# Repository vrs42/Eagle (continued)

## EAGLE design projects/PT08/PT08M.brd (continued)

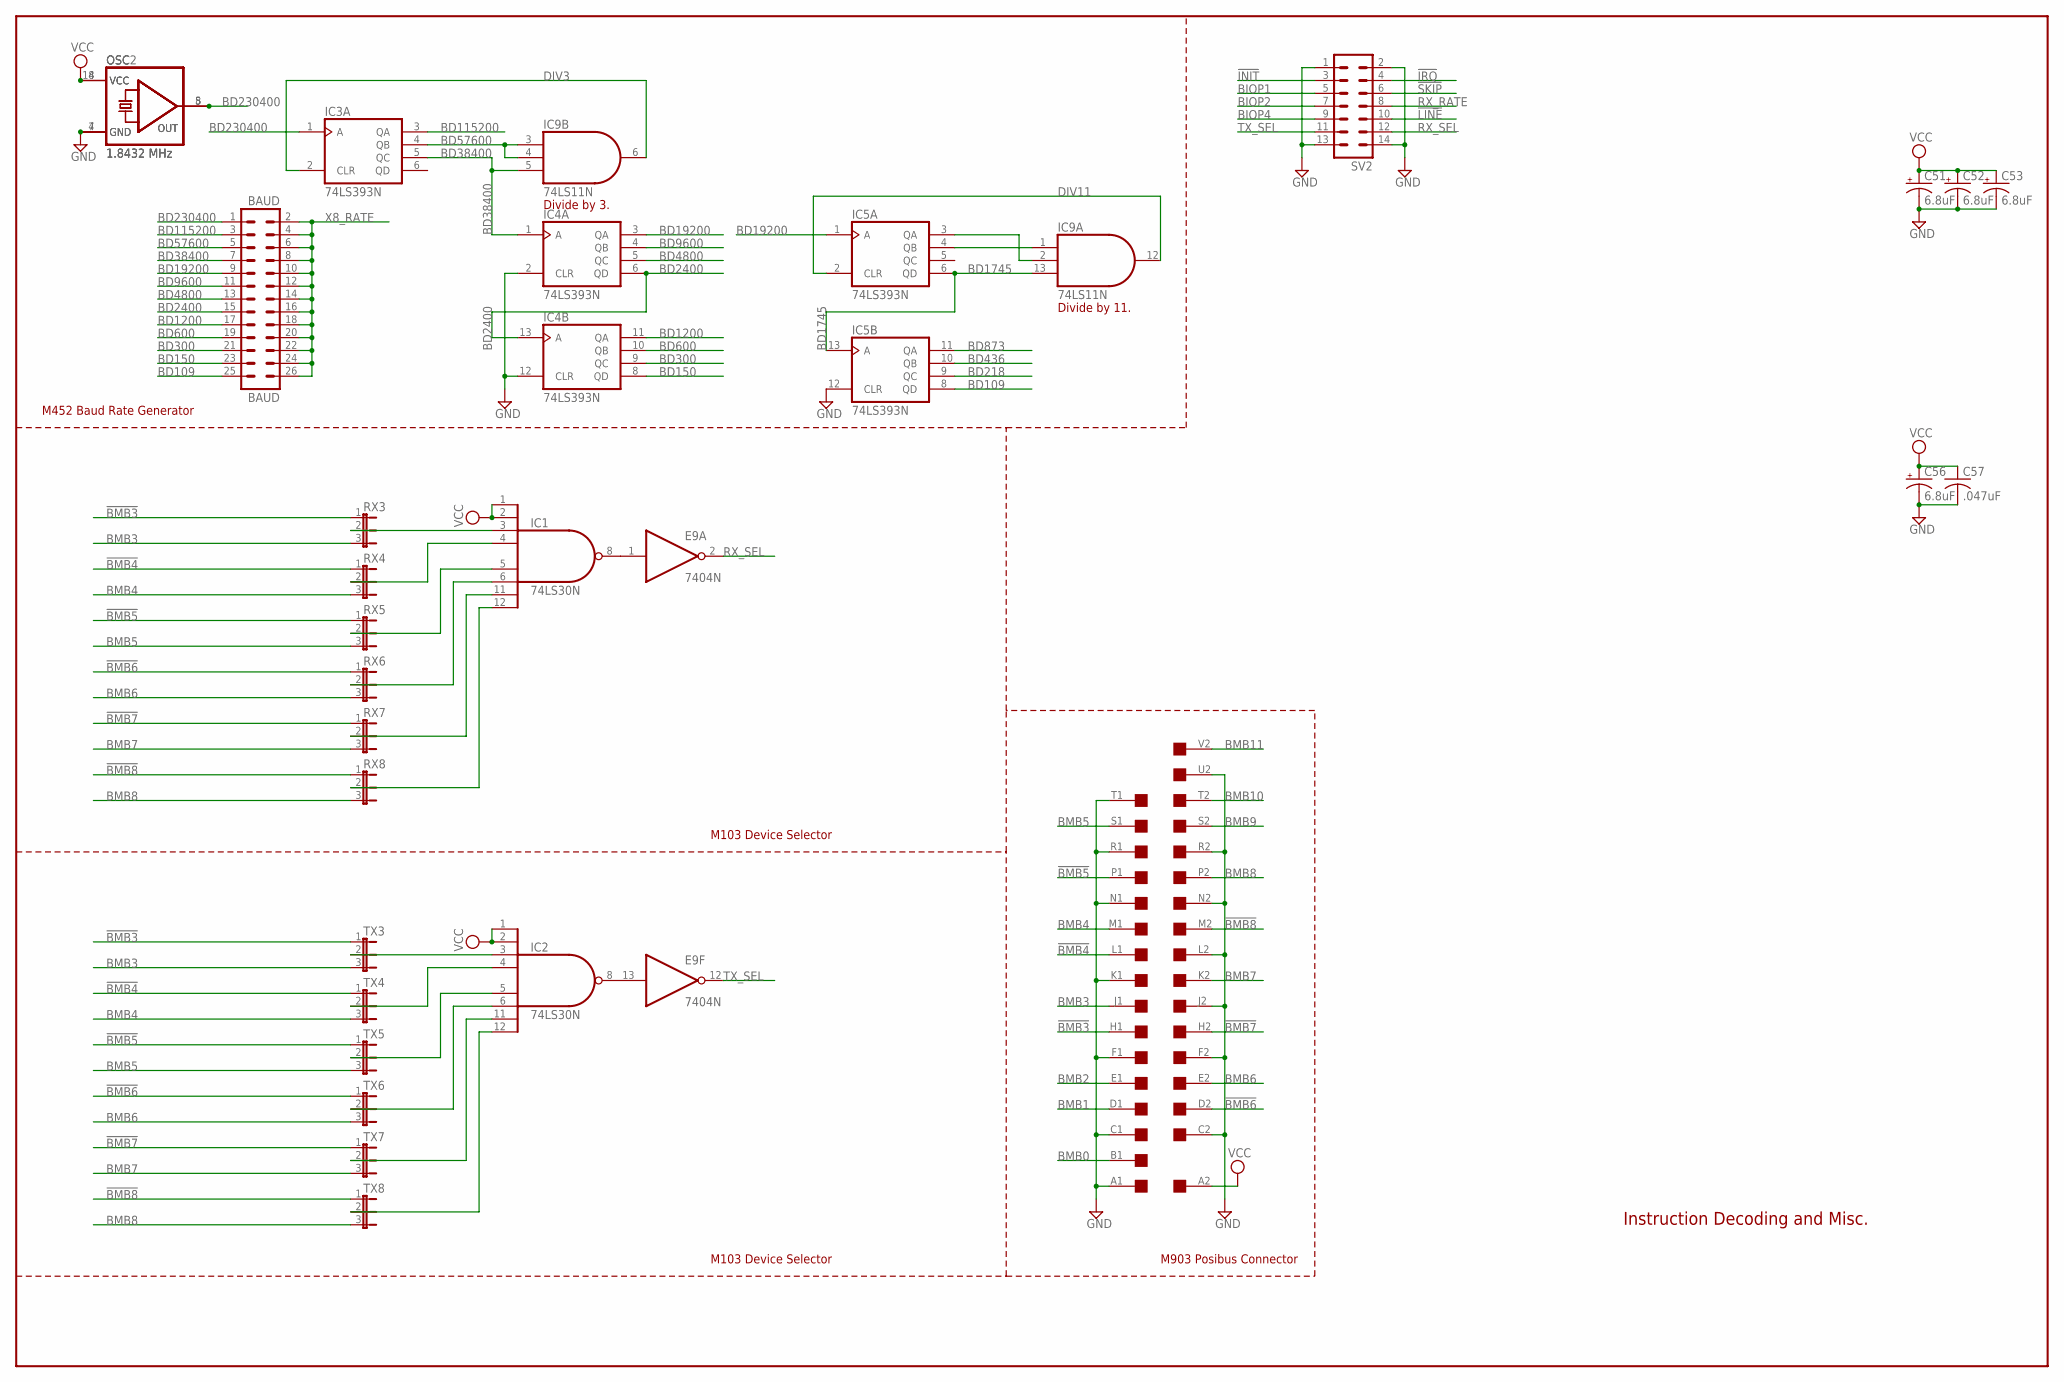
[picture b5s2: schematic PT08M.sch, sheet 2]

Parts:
BAUD: BAUD; MA13-2
C51, C52, C53, C56: 6.8uF; E12-8
C57: .047uF; C050-025X075
E9: 7404N; DIL14
IC1, IC2: 74LS30N; DIL14
IC3, IC4, IC5: 74LS393N; DIL14
IC9: 74LS11N; DIL14
N15: EDGE-2CONNECTOR; EDGE-CON2
OSC: 1.8432 MHz; DIL08S
OSC2: 1.8432 MHz; DIL14S
RX3, RX4, RX5, RX6, RX7, RX8: JP2
SV2: ML14L
TX3, TX4, TX5, TX6, TX7, TX8: JP2

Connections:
!BMB3: N15.H1, RX3.1, TX3.1
!BMB4: N15.L1, RX4.1, TX4.1
!BMB5: N15.P1, RX5.1, TX5.1
!BMB6: N15.D2, RX6.1, TX6.1
!BMB7: N15.H2, RX7.1, TX7.1
!BMB8: N15.M2, RX8.1, TX8.1
!INIT: SV2.3; also elsewhere on the board
!IRQ: SV2.4; also elsewhere on the board
!LINE: SV2.10; also elsewhere on the board
!RX_SEL: E9.1 (I), IC1.8 (O)
!SKIP: SV2.6; also elsewhere on the board
!TX_SEL: E9.13 (I), IC2.8 (O)
BD109: BAUD.25, IC5.8 (QD)
BD150: BAUD.23, IC4.8 (QD)
BD218: IC5.9 (QC)
BD300: BAUD.21, IC4.9 (QC)
BD436: IC5.10 (QB)
BD600: BAUD.19, IC4.10 (QB)
BD873: IC5.11 (QA)
BD1200: BAUD.17, IC4.11 (QA)
BD1745: IC5.6 (QD), IC5.13 (A), IC9.13 (I2)
BD2400: BAUD.15, IC4.6 (QD), IC4.13 (A)
BD4800: BAUD.13, IC4.5 (QC)
BD9600: BAUD.11, IC4.4 (QB)
BD19200: BAUD.9, IC4.3 (QA), IC5.1 (A)
BD38400: BAUD.7, IC3.5 (QC), IC4.1 (A), IC9.5 (I2)
BD57600: BAUD.5, IC3.4 (QB), IC9.3 (I0), IC9.4 (I1)
BD115200: BAUD.3, IC3.3 (QA)
BD230400: BAUD.1, IC3.1 (A), OSC.5 (OUT), OSC2.8 (OUT)
BIOP1: SV2.5; also elsewhere on the board
BIOP2: SV2.7; also elsewhere on the board
BIOP4: SV2.9; also elsewhere on the board
BMB0: N15.B1
BMB1: N15.D1
BMB2: N15.E1
BMB3: N15.J1, RX3.3, TX3.3
BMB4: N15.M1, RX4.3, TX4.3
BMB5: N15.S1, RX5.3, TX5.3
BMB6: N15.E2, RX6.3, TX6.3
BMB7: N15.K2, RX7.3, TX7.3
BMB8: N15.P2, RX8.3, TX8.3
BMB9: N15.S2
BMB10: N15.T2
BMB11: N15.V2
DIV3: IC3.2 (CLR), IC9.6 (O)
DIV11: IC5.2 (CLR), IC9.12 (O)
GND: C51.-, C52.-, C53.-, C56.-, C57.2, E9.7 (GND), IC1.7 (GND), IC2.7 (GND), IC3.7 (GND), IC4.2 (CLR), IC4.7 (GND), IC4.12 (CLR), IC5.7 (GND), IC5.12 (CLR), IC9.7 (GND), N15.A1, N15.C1, N15.C2, N15.F1, N15.F2, N15.J2, N15.K1, N15.L2, N15.N1, N15.N2, N15.R1, N15.R2, N15.T1, N15.U2, OSC.4 (GND), OSC2.7 (GND), SV2.1, SV2.2, SV2.13, SV2.14; also elsewhere on the board
unnamed: IC2.4 (I3), TX4.2
unnamed: IC1.3 (I2), RX3.2
unnamed: IC1.4 (I3), RX4.2
unnamed: IC2.6 (I5), TX6.2
unnamed: IC1.5 (I4), RX5.2
unnamed: IC2.5 (I4), TX5.2
unnamed: IC2.12 (I7), TX8.2
unnamed: IC2.11 (I6), TX7.2
unnamed: IC5.3 (QA), IC9.2 (I1)
unnamed: IC2.3 (I2), TX3.2
unnamed: IC1.12 (I7), RX8.2
unnamed: IC5.4 (QB), IC9.1 (I0)
unnamed: IC1.11 (I6), RX7.2
unnamed: IC1.6 (I5), RX6.2
RX_RATE: SV2.8; also elsewhere on the board
RX_SEL: E9.2 (O), SV2.12; also elsewhere on the board
TX_SEL: E9.12 (O), SV2.11; also elsewhere on the board
VCC: C51.+, C52.+, C53.+, C56.+, C57.1, E9.14 (VCC), IC1.1 (I0), IC1.2 (I1), IC1.14 (VCC), IC2.1 (I0), IC2.2 (I1), IC2.14 (VCC), IC3.14 (VCC), IC4.14 (VCC), IC5.14 (VCC), IC9.14 (VCC), N15.A2, OSC.8 (VCC), OSC2.14 (VCC); also elsewhere on the board
X8_RATE: BAUD.2, BAUD.4, BAUD.6, BAUD.8, BAUD.10, BAUD.12, BAUD.14, BAUD.16, BAUD.18, BAUD.20, BAUD.22, BAUD.24, BAUD.26

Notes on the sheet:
Instruction Decoding and Misc.
M452 Baud Rate Generator
M103 Device Selector
M903 Posibus Connector
Divide by 11.
Divide by 3.

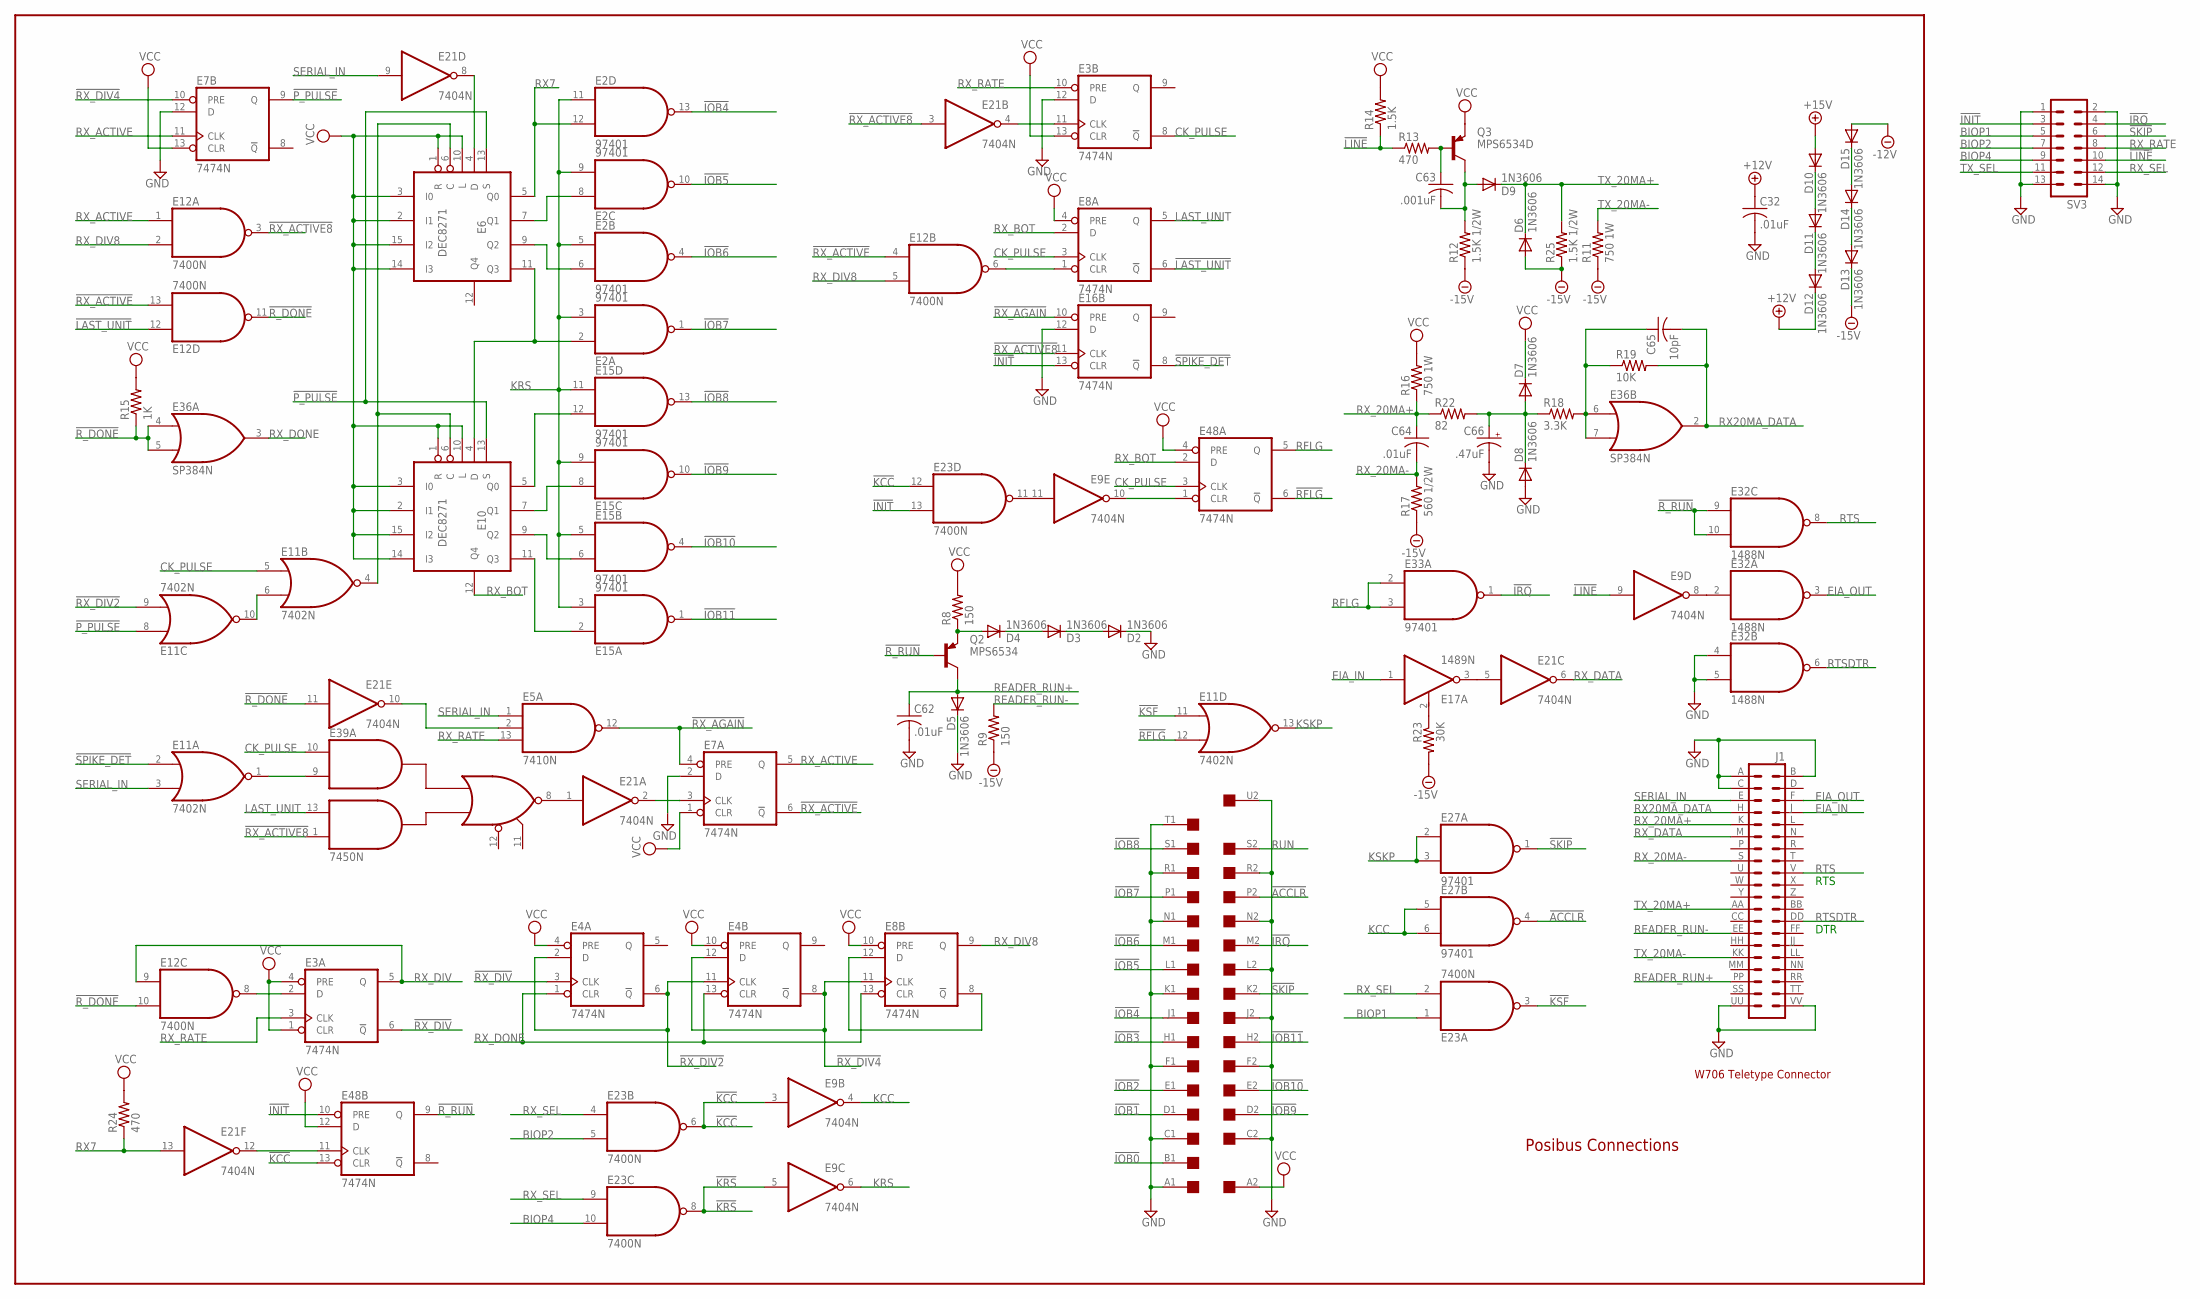
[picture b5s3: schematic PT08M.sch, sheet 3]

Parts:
C32, C62, C64: .01uF; C050-025X075
C63: .001uF; C050-025X075
C65: 10pF; C050-025X075
C66: .47uF; E15-5
D2, D3, D4, D5, D6, D7, D8, D9, D10, D11, D12, D13, D14, D15: 1N3606; DO35-10
E2, E15, E27, E33: 97401; DIL14
E3, E4, E7, E8, E16, E48: 7474N; DIL14
E5: 7410N; DIL14
E6, E10: DEC8271; DIL16
E9, E21: 7404N; DIL14
E11: 7402N; DIL14
E12, E23: 7400N; DIL14
E17: 1489N; DIL14
E32: 1488N; DIL14
E36: SP384N; DIL14
E39: 7450N; DIL14
J1: DEC40PINH
N16: EDGE-2CONNECTOR; EDGE-CON2
Q2: MPS6534; TO5
Q3: MPS6534D; TO5
R8, R9: 150; 0207/10
R11, R16: 750 1W; 0617/17
R12, R25: 1.5K 1/2W; 0411/15
R13, R24: 470; 0207/10
R14: 1.5K; 0207/10
R15: 1K; 0207/10
R17: 560 1/2W; 0411/15
R18: 3.3K; 0207/10
R19: 10K; 0207/10
R22: 82; 0207/10
R23: 30K; 0207/10
SV3: ML14L

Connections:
!ACCLR: E27.4 (O), N16.P2
!INIT: E16.13 (CLR), E23.13 (I1), E48.10 (PRE), SV3.3; also elsewhere on the board
!IOB0: N16.B1
!IOB1: N16.D1
!IOB2: N16.E1
!IOB3: N16.H1
!IOB4: E2.13 (O), N16.J1
!IOB5: E2.10 (O), N16.L1
!IOB6: E2.4 (O), N16.M1
!IOB7: E2.1 (O), N16.P1
!IOB8: E15.13 (O), N16.S1
!IOB9: E15.10 (O), N16.D2
!IOB10: E15.4 (O), N16.E2
!IOB11: E15.1 (O), N16.H2
!IRQ: E33.1 (O), N16.M2, SV3.4; also elsewhere on the board
!KCC: E9.3 (I), E23.6 (O), E23.12 (I0), E48.13 (CLR)
!KRS: E9.5 (I), E23.8 (O)
!KSF: E11.11 (I0), E23.3 (O)
!LAST_UNIT: E8.6 (!Q), E12.12 (I0)
!LINE: E9.9 (I), R13.1, R14.1, SV3.10; also elsewhere on the board
!P_PULSE: E6.13 (S), E7.9 (Q), E10.13 (S), E11.8 (I0)
!RFLG: E11.12 (I1), E48.6 (!Q)
!RX_ACTIVE: E7.6 (!Q), E12.4 (I0), E12.13 (I1)
!RX_ACTIVE8: E12.3 (O), E16.11 (CLK), E21.3 (I), E39.1 (I4)
!RX_AGAIN: E5.12 (O), E7.4 (PRE), E16.10 (PRE)
!RX_DIV: E3.6 (!Q), E4.3 (CLK)
!RX_DIV2: E4.2 (D), E4.6 (!Q), E4.11 (CLK), E11.9 (I1)
!RX_DIV4: E4.8 (!Q), E4.12 (D), E7.10 (PRE), E8.11 (CLK)
!R_DONE: E12.10 (I1), E12.11 (O), E21.11 (I), E36.4 (I0), E36.5 (I1), R15.1
!R_RUN: E32.9 (I0), E32.10 (I1), E48.9 (Q), Q2.2 (B)
!SKIP: E27.1 (O), N16.K2, SV3.6; also elsewhere on the board
!SPIKE_DET: E11.2 (I0), E16.8 (!Q)
+12V: C32.1, D12.C, E32.14 (+12V)
+15V: D10.A
-12V: D15.A, E32.1 (-12V)
-15V: D6.A, D13.C, R9.1, R11.1, R12.1, R17.1, R23.2, R25.1
BIOP1: E23.1 (I0), SV3.5; also elsewhere on the board
BIOP2: E23.5 (I1), SV3.7; also elsewhere on the board
BIOP4: E23.10 (I1), SV3.9; also elsewhere on the board
CK_PULSE: E3.8 (!Q), E8.3 (CLK), E11.5 (I0), E39.10 (I1), E48.3 (CLK)
EIA_IN: E17.1 (I), J1.J (8)
EIA_OUT: E32.3 (O), J1.F (6)
GND: C32.2, C62.2, C66.-, D2.C, D5.C, D8.A, E2.7 (GND), E3.7 (GND), E3.12 (D), E4.7 (GND), E5.7 (GND), E6.8 (GND), E7.2 (D), E7.7 (GND), E7.12 (D), E8.7 (GND), E9.7 (GND), E10.8 (GND), E11.7 (GND), E12.7 (GND), E15.7 (GND), E16.7 (GND), E16.12 (D), E17.7 (GND), E21.7 (GND), E23.7 (GND), E27.7 (GND), E32.4 (I0), E32.5 (I1), E32.7 (GND), E33.7 (GND), E36.1 (GND), E39.7 (GND), E48.7 (GND), J1.A (1), J1.B (2), J1.C (3), J1.UU (39), J1.VV (40), N16.A1, N16.C1, N16.C2, N16.F1, N16.F2, N16.J2, N16.K1, N16.L2, N16.N1, N16.N2, N16.R1, N16.R2, N16.T1, N16.U2, SV3.1, SV3.2, SV3.13, SV3.14; also elsewhere on the board
KCC: E9.4 (O), E27.5 (I0), E27.6 (I1)
KRS: E2.3 (I1), E2.5 (I0), E2.9 (I1), E2.11 (I0), E9.6 (O), E15.3 (I1), E15.5 (I0), E15.9 (I1), E15.11 (I0)
KSKP: E11.13 (O), E27.2 (I0), E27.3 (I1)
LAST_UNIT: E8.5 (Q), E39.13 (I3)
unnamed: E9.8 (O), E32.2 (I)
unnamed: E21.12 (O), E48.11 (CLK)
unnamed: E9.10 (O), E48.1 (CLR)
unnamed: E9.11 (I), E23.11 (O)
unnamed: D2.A, D3.C
unnamed: E2.8 (I0), E6.7 (Q1)
unnamed: E2.2 (I0), E6.11 (Q3), E10.4 (D)
unnamed: E2.6 (I1), E6.9 (Q2)
unnamed: E10.5 (Q0), E15.12 (I1)
unnamed: E10.7 (Q1), E15.8 (I0)
unnamed: E10.9 (Q2), E15.6 (I1)
unnamed: E10.11 (Q3), E15.2 (I0)
unnamed: E6.6 (C), E10.6 (C), E11.4 (O)
unnamed: E11.6 (I1), E11.10 (O)
unnamed: E6.4 (D), E21.8 (O)
unnamed: E7.3 (CLK), E21.2 (O)
unnamed: E21.1 (I), E39.8 (O)
unnamed: C63.2, D9.A, Q3.3 (C), R12.2
unnamed: E3.2 (D), E12.8 (O)
unnamed: E17.2 (RC), R23.1
unnamed: E5.2 (I1), E21.10 (O)
unnamed: D13.A, D14.C
unnamed: E11.1 (O), E39.9 (I2)
unnamed: E3.11 (CLK), E21.4 (O)
unnamed: E17.3 (O), E21.5 (I)
unnamed: E8.8 (!Q), E8.12 (D)
unnamed: E8.1 (CLR), E12.6 (O)
unnamed: D4.A, Q2.1 (E), R8.1
unnamed: D3.A, D4.C
unnamed: D14.A, D15.C
unnamed: C66.+, D7.A, D8.C, R18.1, R22.2
unnamed: D10.C, D11.A
unnamed: D11.C, D12.A
unnamed: C65.1, E36.6 (I0), E36.7 (I1), R18.2, R19.1
unnamed: C63.1, Q3.2 (B), R13.2
READER_RUN+: C62.1, D5.A, J1.PP (35), Q2.3 (C)
READER_RUN-: J1.EE (27), R9.2
RFLG: E33.2 (I0), E33.3 (I1), E48.5 (Q)
RTS: E32.8 (O), J1.V (18)
RTSDTR: E32.6 (O), J1.DD (26)
RUN: N16.S2
RX7: E2.12 (I1), E6.5 (Q0), E21.13 (I), R24.1
RX20MA_DATA: C65.2, E36.2 (O), J1.H (7), R19.2
RX_20MA+: C64.1, J1.K (9), R16.1, R22.1
RX_20MA-: C64.2, J1.S (15), R17.2
RX_ACTIVE: E7.5 (Q), E7.11 (CLK), E12.1 (I0)
RX_BOT: E8.2 (D), E10.12 (Q4), E48.2 (D)
RX_DATA: E21.6 (O), J1.M (11)
RX_DIV: E3.5 (Q), E12.9 (I0)
RX_DIV8: E8.9 (Q), E12.2 (I1), E12.5 (I1)
RX_DONE: E4.1 (CLR), E4.13 (CLR), E8.13 (CLR), E36.3 (O)
RX_RATE: E3.3 (CLK), E3.10 (PRE), E5.13 (I2), SV3.8; also elsewhere on the board
RX_SEL: E23.2 (I1), E23.4 (I0), E23.9 (I0), SV3.12; also elsewhere on the board
SERIAL_IN: E5.1 (I0), E11.3 (I1), E21.9 (I), J1.E (5)
TX_20MA+: D6.C, D9.C, J1.AA (23), R25.2
TX_20MA-: J1.KK (31), R11.2
TX_SEL: SV3.11; also elsewhere on the board
VCC: D7.C, E2.14 (VCC), E3.1 (CLR), E3.4 (PRE), E3.13 (CLR), E3.14 (VCC), E4.4 (PRE), E4.10 (PRE), E4.14 (VCC), E5.14 (VCC), E6.1 (R), E6.2 (I1), E6.3 (I0), E6.10 (L), E6.14 (I3), E6.15 (I2), E6.16 (VCC), E7.1 (CLR), E7.13 (CLR), E7.14 (VCC), E8.4 (PRE), E8.10 (PRE), E8.14 (VCC), E9.14 (VCC), E10.1 (R), E10.2 (I1), E10.3 (I0), E10.10 (L), E10.14 (I3), E10.15 (I2), E10.16 (VCC), E11.14 (VCC), E12.14 (VCC), E15.14 (VCC), E16.14 (VCC), E17.14 (VCC), E21.14 (VCC), E23.14 (VCC), E27.14 (VCC), E33.14 (VCC), E36.8 (VCC), E39.14 (VCC), E48.4 (PRE), E48.12 (D), E48.14 (VCC), N16.A2, Q3.1 (E), R8.2, R14.2, R15.2, R16.2, R24.2; also elsewhere on the board

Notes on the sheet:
Posibus Connections
RTS
DTR
W706 Teletype Connector

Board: 4 copper layers, 143 parts (0 on the bottom side), 190 nets, no tracks yet.

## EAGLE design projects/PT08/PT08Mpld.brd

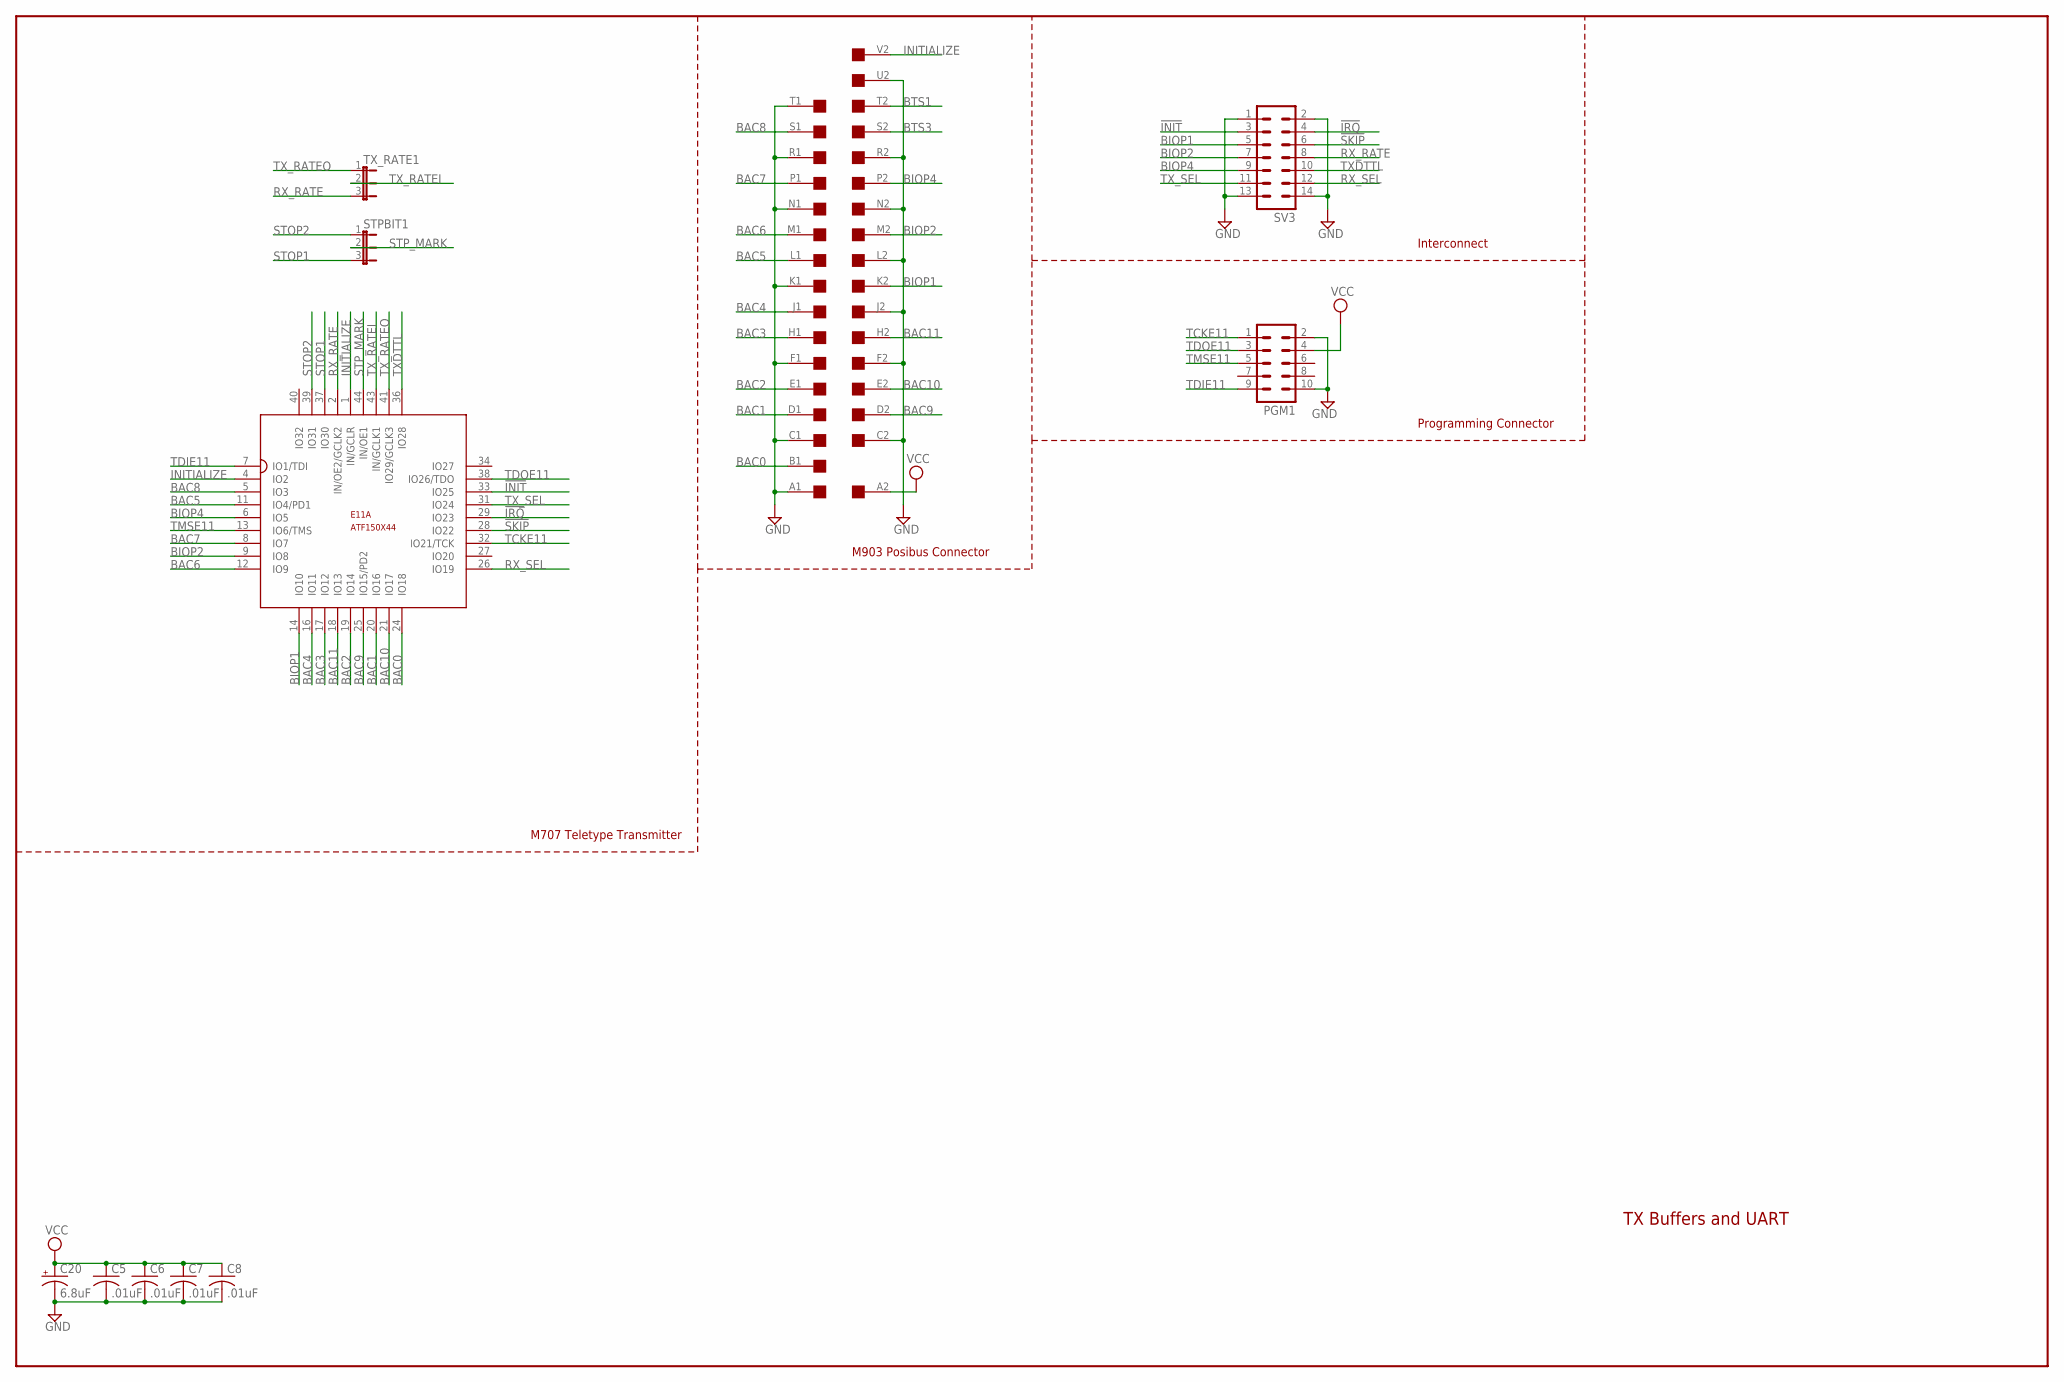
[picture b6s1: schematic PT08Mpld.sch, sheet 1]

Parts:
BAC: EDGE-2CONNECTOR; EDGE-CON2
C5, C6, C7, C8: .01uF; C050-025X075
C20: 6.8uF; E12-8
E11: ATF150X44; 3M44
PGM1: ML10
STPBIT1: JP2
SV3: ML14L
TX_RATE1: JP2

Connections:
!INIT: E11.33 (IO25), SV3.3; also elsewhere on the board
!IRQ: E11.29 (IO23), SV3.4; also elsewhere on the board
!SKIP: E11.28 (IO22), SV3.6; also elsewhere on the board
BAC0: BAC.B1, E11.24 (IO18)
BAC1: BAC.D1, E11.20 (IO16)
BAC2: BAC.E1, E11.19 (IO14)
BAC3: BAC.H1, E11.17 (IO12)
BAC4: BAC.J1, E11.16 (IO11)
BAC5: BAC.L1, E11.11 (IO4/PD1)
BAC6: BAC.M1, E11.12 (IO9)
BAC7: BAC.P1, E11.8 (IO7)
BAC8: BAC.S1, E11.5 (IO3)
BAC9: BAC.D2, E11.25 (IO15/PD2)
BAC10: BAC.E2, E11.21 (IO17)
BAC11: BAC.H2, E11.18 (IO13)
BIOP1: BAC.K2, E11.14 (IO10), SV3.5; also elsewhere on the board
BIOP2: BAC.M2, E11.9 (IO8), SV3.7; also elsewhere on the board
BIOP4: BAC.P2, E11.6 (IO5), SV3.9; also elsewhere on the board
BTS1: BAC.T2
BTS3: BAC.S2
GND: BAC.A1, BAC.C1, BAC.C2, BAC.F1, BAC.F2, BAC.J2, BAC.K1, BAC.L2, BAC.N1, BAC.N2, BAC.R1, BAC.R2, BAC.T1, BAC.U2, C5.2, C6.2, C7.2, C8.2, C20.-, E11.10 (GND), E11.22 (GND), E11.30 (GND), E11.42 (GND), PGM1.2, PGM1.10, SV3.1, SV3.2, SV3.13, SV3.14; also elsewhere on the board
INITIALIZE: BAC.V2, E11.1 (IN/GCLR), E11.4 (IO2)
RX_RATE: E11.2 (IN/OE2/GCLK2), SV3.8, TX_RATE1.3; also elsewhere on the board
RX_SEL: E11.26 (IO19), SV3.12; also elsewhere on the board
STOP1: E11.37 (IO30), STPBIT1.3
STOP2: E11.39 (IO31), STPBIT1.1
STP_MARK: E11.44 (IN/OE1), STPBIT1.2
TCKE11: E11.32 (IO21/TCK), PGM1.1
TDIE11: E11.7 (IO1/TDI), PGM1.9
TDOE11: E11.38 (IO26/TDO), PGM1.3
TMSE11: E11.13 (IO6/TMS), PGM1.5
TXDTTL: E11.36 (IO28), SV3.10; also elsewhere on the board
TX_RATEI: E11.43 (IN/GCLK1), TX_RATE1.2
TX_RATEO: E11.41 (IO29/GCLK3), TX_RATE1.1
TX_SEL: E11.31 (IO24), SV3.11; also elsewhere on the board
VCC: BAC.A2, C5.1, C6.1, C7.1, C8.1, C20.+, E11.3 (VCC), E11.15 (VCC), E11.23 (VCC), E11.35 (VCC), PGM1.4; also elsewhere on the board

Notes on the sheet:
TX Buffers and UART
M707 Teletype Transmitter
M903 Posibus Connector
Programming Connector
Interconnect

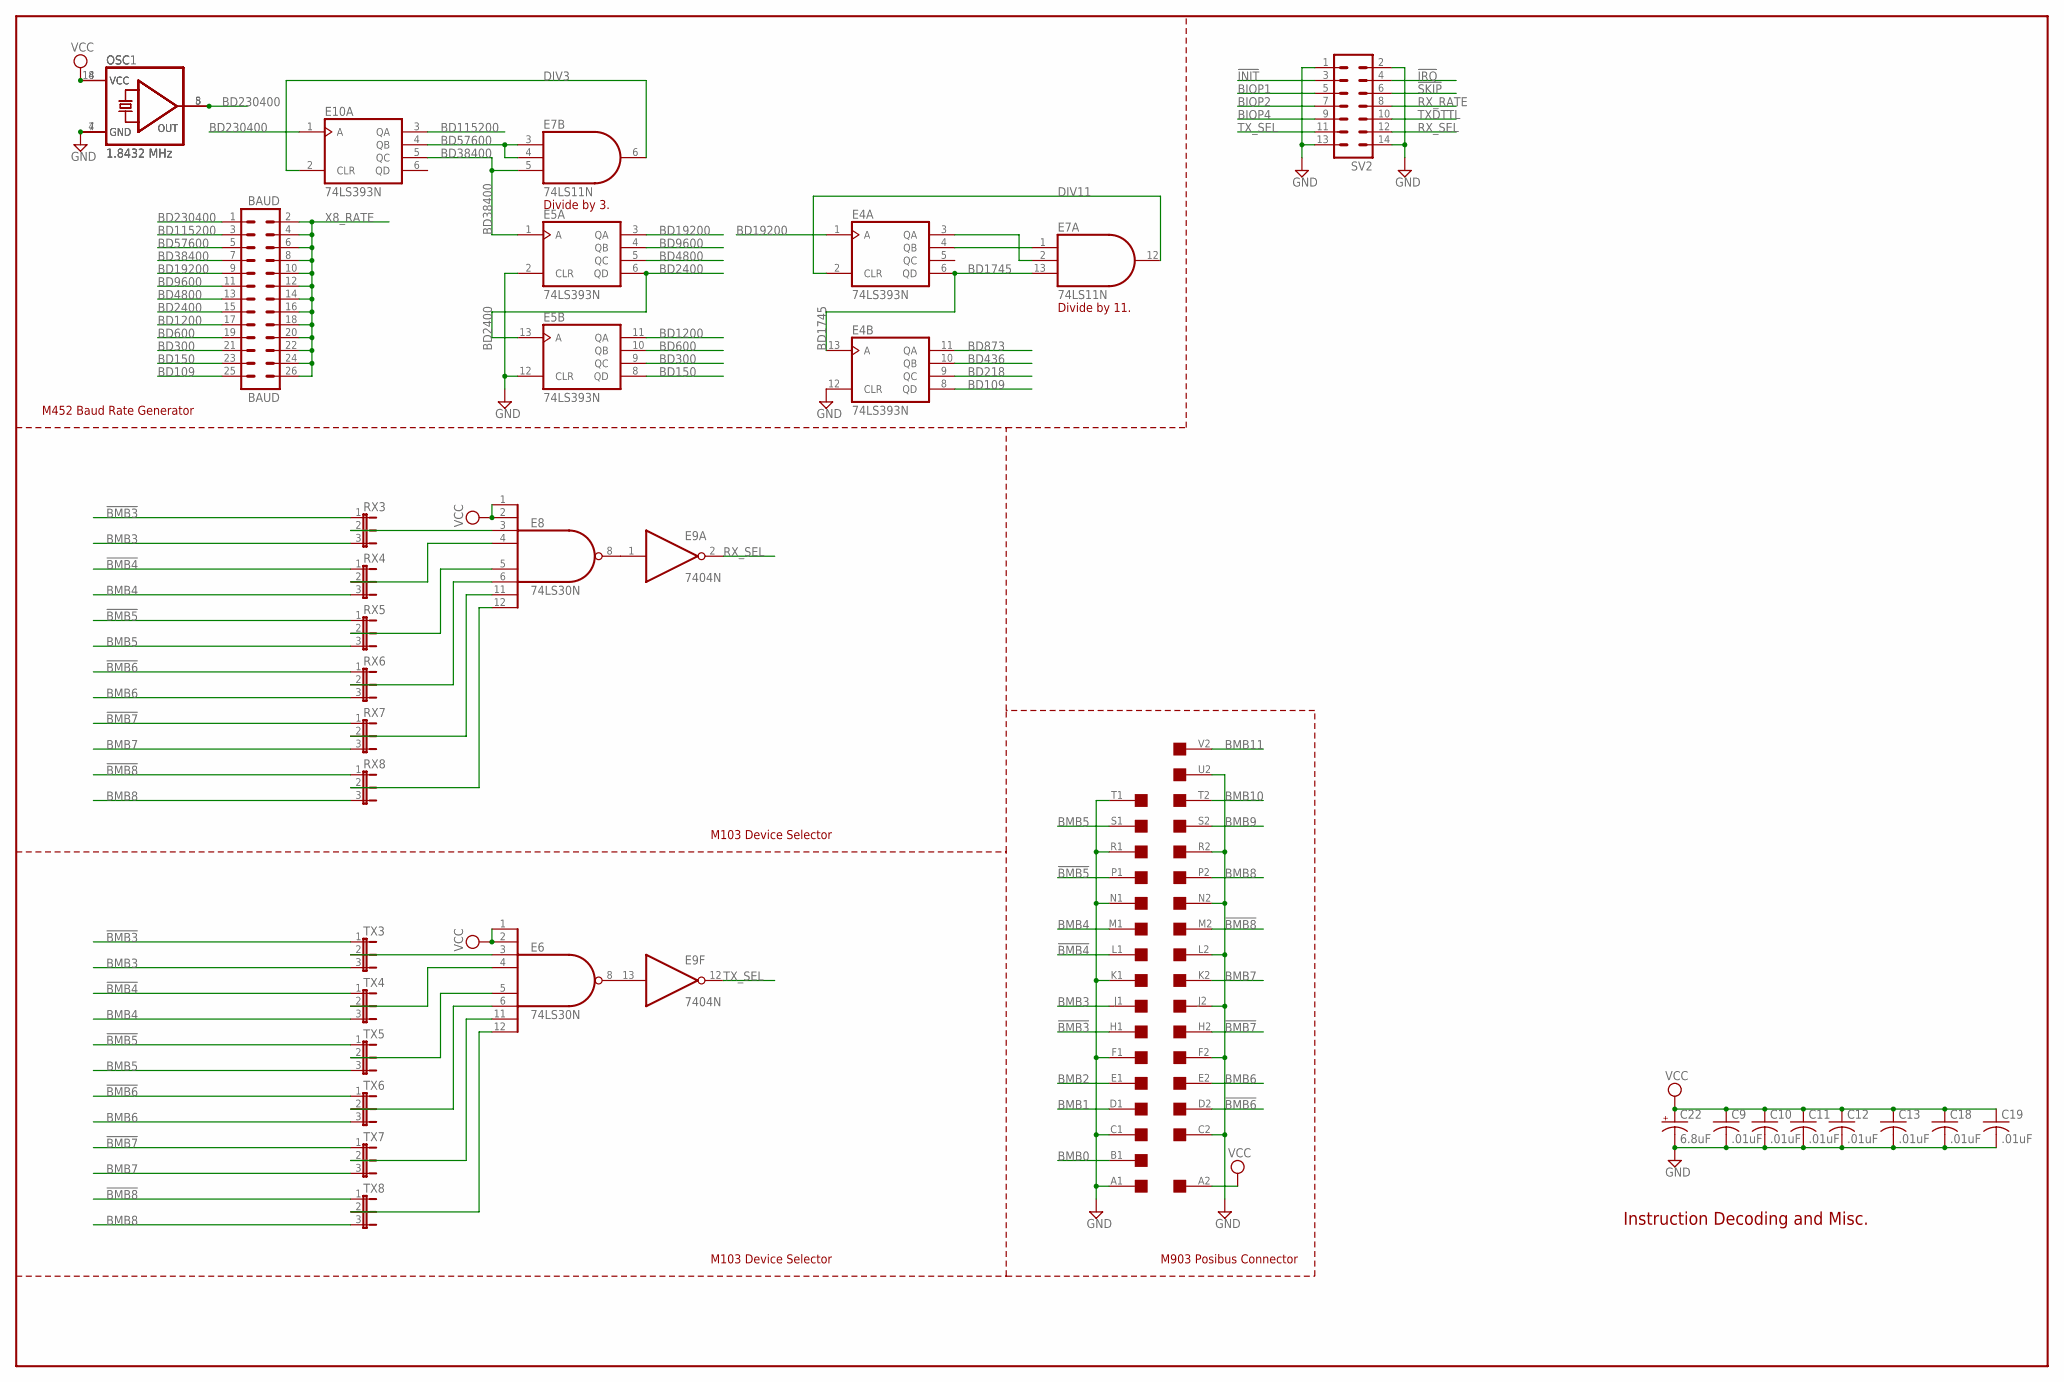
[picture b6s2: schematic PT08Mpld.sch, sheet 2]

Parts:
BAUD: BAUD; MA13-2
BMB: EDGE-2CONNECTOR; EDGE-CON2
C9, C10, C11, C12, C13, C18, C19: .01uF; C050-025X075
C22: 6.8uF; E12-8
E4, E5, E10: 74LS393N; DIL14
E6, E8: 74LS30N; DIL14
E7: 74LS11N; DIL14
E9: 7404N; DIL14
OSC: 1.8432 MHz; DIL08S
OSC1: 1.8432 MHz; DIL14S
RX3, RX4, RX5, RX6, RX7, RX8: JP2
SV2: ML14L
TX3, TX4, TX5, TX6, TX7, TX8: JP2

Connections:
!BMB3: BMB.H1, RX3.1, TX3.1
!BMB4: BMB.L1, RX4.1, TX4.1
!BMB5: BMB.P1, RX5.1, TX5.1
!BMB6: BMB.D2, RX6.1, TX6.1
!BMB7: BMB.H2, RX7.1, TX7.1
!BMB8: BMB.M2, RX8.1, TX8.1
!INIT: SV2.3; also elsewhere on the board
!IRQ: SV2.4; also elsewhere on the board
!RX_SEL: E8.8 (O), E9.1 (I)
!SKIP: SV2.6; also elsewhere on the board
!TX_SEL: E6.8 (O), E9.13 (I)
BD109: BAUD.25, E4.8 (QD)
BD150: BAUD.23, E5.8 (QD)
BD218: E4.9 (QC)
BD300: BAUD.21, E5.9 (QC)
BD436: E4.10 (QB)
BD600: BAUD.19, E5.10 (QB)
BD873: E4.11 (QA)
BD1200: BAUD.17, E5.11 (QA)
BD1745: E4.6 (QD), E4.13 (A), E7.13 (I2)
BD2400: BAUD.15, E5.6 (QD), E5.13 (A)
BD4800: BAUD.13, E5.5 (QC)
BD9600: BAUD.11, E5.4 (QB)
BD19200: BAUD.9, E4.1 (A), E5.3 (QA)
BD38400: BAUD.7, E5.1 (A), E7.5 (I2), E10.5 (QC)
BD57600: BAUD.5, E7.3 (I0), E7.4 (I1), E10.4 (QB)
BD115200: BAUD.3, E10.3 (QA)
BD230400: BAUD.1, E10.1 (A), OSC.5 (OUT), OSC1.8 (OUT)
BIOP1: SV2.5; also elsewhere on the board
BIOP2: SV2.7; also elsewhere on the board
BIOP4: SV2.9; also elsewhere on the board
BMB0: BMB.B1
BMB1: BMB.D1
BMB2: BMB.E1
BMB3: BMB.J1, RX3.3, TX3.3
BMB4: BMB.M1, RX4.3, TX4.3
BMB5: BMB.S1, RX5.3, TX5.3
BMB6: BMB.E2, RX6.3, TX6.3
BMB7: BMB.K2, RX7.3, TX7.3
BMB8: BMB.P2, RX8.3, TX8.3
BMB9: BMB.S2
BMB10: BMB.T2
BMB11: BMB.V2
DIV3: E7.6 (O), E10.2 (CLR)
DIV11: E4.2 (CLR), E7.12 (O)
GND: BMB.A1, BMB.C1, BMB.C2, BMB.F1, BMB.F2, BMB.J2, BMB.K1, BMB.L2, BMB.N1, BMB.N2, BMB.R1, BMB.R2, BMB.T1, BMB.U2, C9.2, C10.2, C11.2, C12.2, C13.2, C18.2, C19.2, C22.-, E4.7 (GND), E4.12 (CLR), E5.2 (CLR), E5.7 (GND), E5.12 (CLR), E6.7 (GND), E7.7 (GND), E8.7 (GND), E9.7 (GND), E10.7 (GND), OSC.4 (GND), OSC1.7 (GND), SV2.1, SV2.2, SV2.13, SV2.14; also elsewhere on the board
unnamed: E4.3 (QA), E7.2 (I1)
unnamed: E4.4 (QB), E7.1 (I0)
RX3: E8.3 (I2), RX3.2
RX4: E8.4 (I3), RX4.2
RX5: E8.5 (I4), RX5.2
RX6: E8.6 (I5), RX6.2
RX7: E8.11 (I6), RX7.2
RX8: E8.12 (I7), RX8.2
RX_RATE: SV2.8; also elsewhere on the board
RX_SEL: E9.2 (O), SV2.12; also elsewhere on the board
TX3: E6.3 (I2), TX3.2
TX4: E6.4 (I3), TX4.2
TX5: E6.5 (I4), TX5.2
TX6: E6.6 (I5), TX6.2
TX7: E6.11 (I6), TX7.2
TX8: E6.12 (I7), TX8.2
TXDTTL: SV2.10; also elsewhere on the board
TX_SEL: E9.12 (O), SV2.11; also elsewhere on the board
VCC: BMB.A2, C9.1, C10.1, C11.1, C12.1, C13.1, C18.1, C19.1, C22.+, E4.14 (VCC), E5.14 (VCC), E6.1 (I0), E6.2 (I1), E6.14 (VCC), E7.14 (VCC), E8.1 (I0), E8.2 (I1), E8.14 (VCC), E9.14 (VCC), E10.14 (VCC), OSC.8 (VCC), OSC1.14 (VCC); also elsewhere on the board
X8_RATE: BAUD.2, BAUD.4, BAUD.6, BAUD.8, BAUD.10, BAUD.12, BAUD.14, BAUD.16, BAUD.18, BAUD.20, BAUD.22, BAUD.24, BAUD.26

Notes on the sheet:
Instruction Decoding and Misc.
M452 Baud Rate Generator
M103 Device Selector
M903 Posibus Connector
Divide by 11.
Divide by 3.
